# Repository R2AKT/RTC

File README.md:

License addendum - https://github.com/R2AKT/RTC/blob/main/Addendum.txt
# RTC
Real-time clock module (RTC). For connection to the CPU_8080 processor board - https://github.com/R2AKT/CPU_8080.

Based on a real-time clock for RADIO-86RK.

Status: testing and writing the driver.

Модуль часов реального времени (RTC). Для подключения к процессорной плате CPU_8080 - https://github.com/R2AKT/CPU_8080.

На базе часов реального времени для РАДИО-86РК.

Статус: в процессе тестирования и написания драйвера.

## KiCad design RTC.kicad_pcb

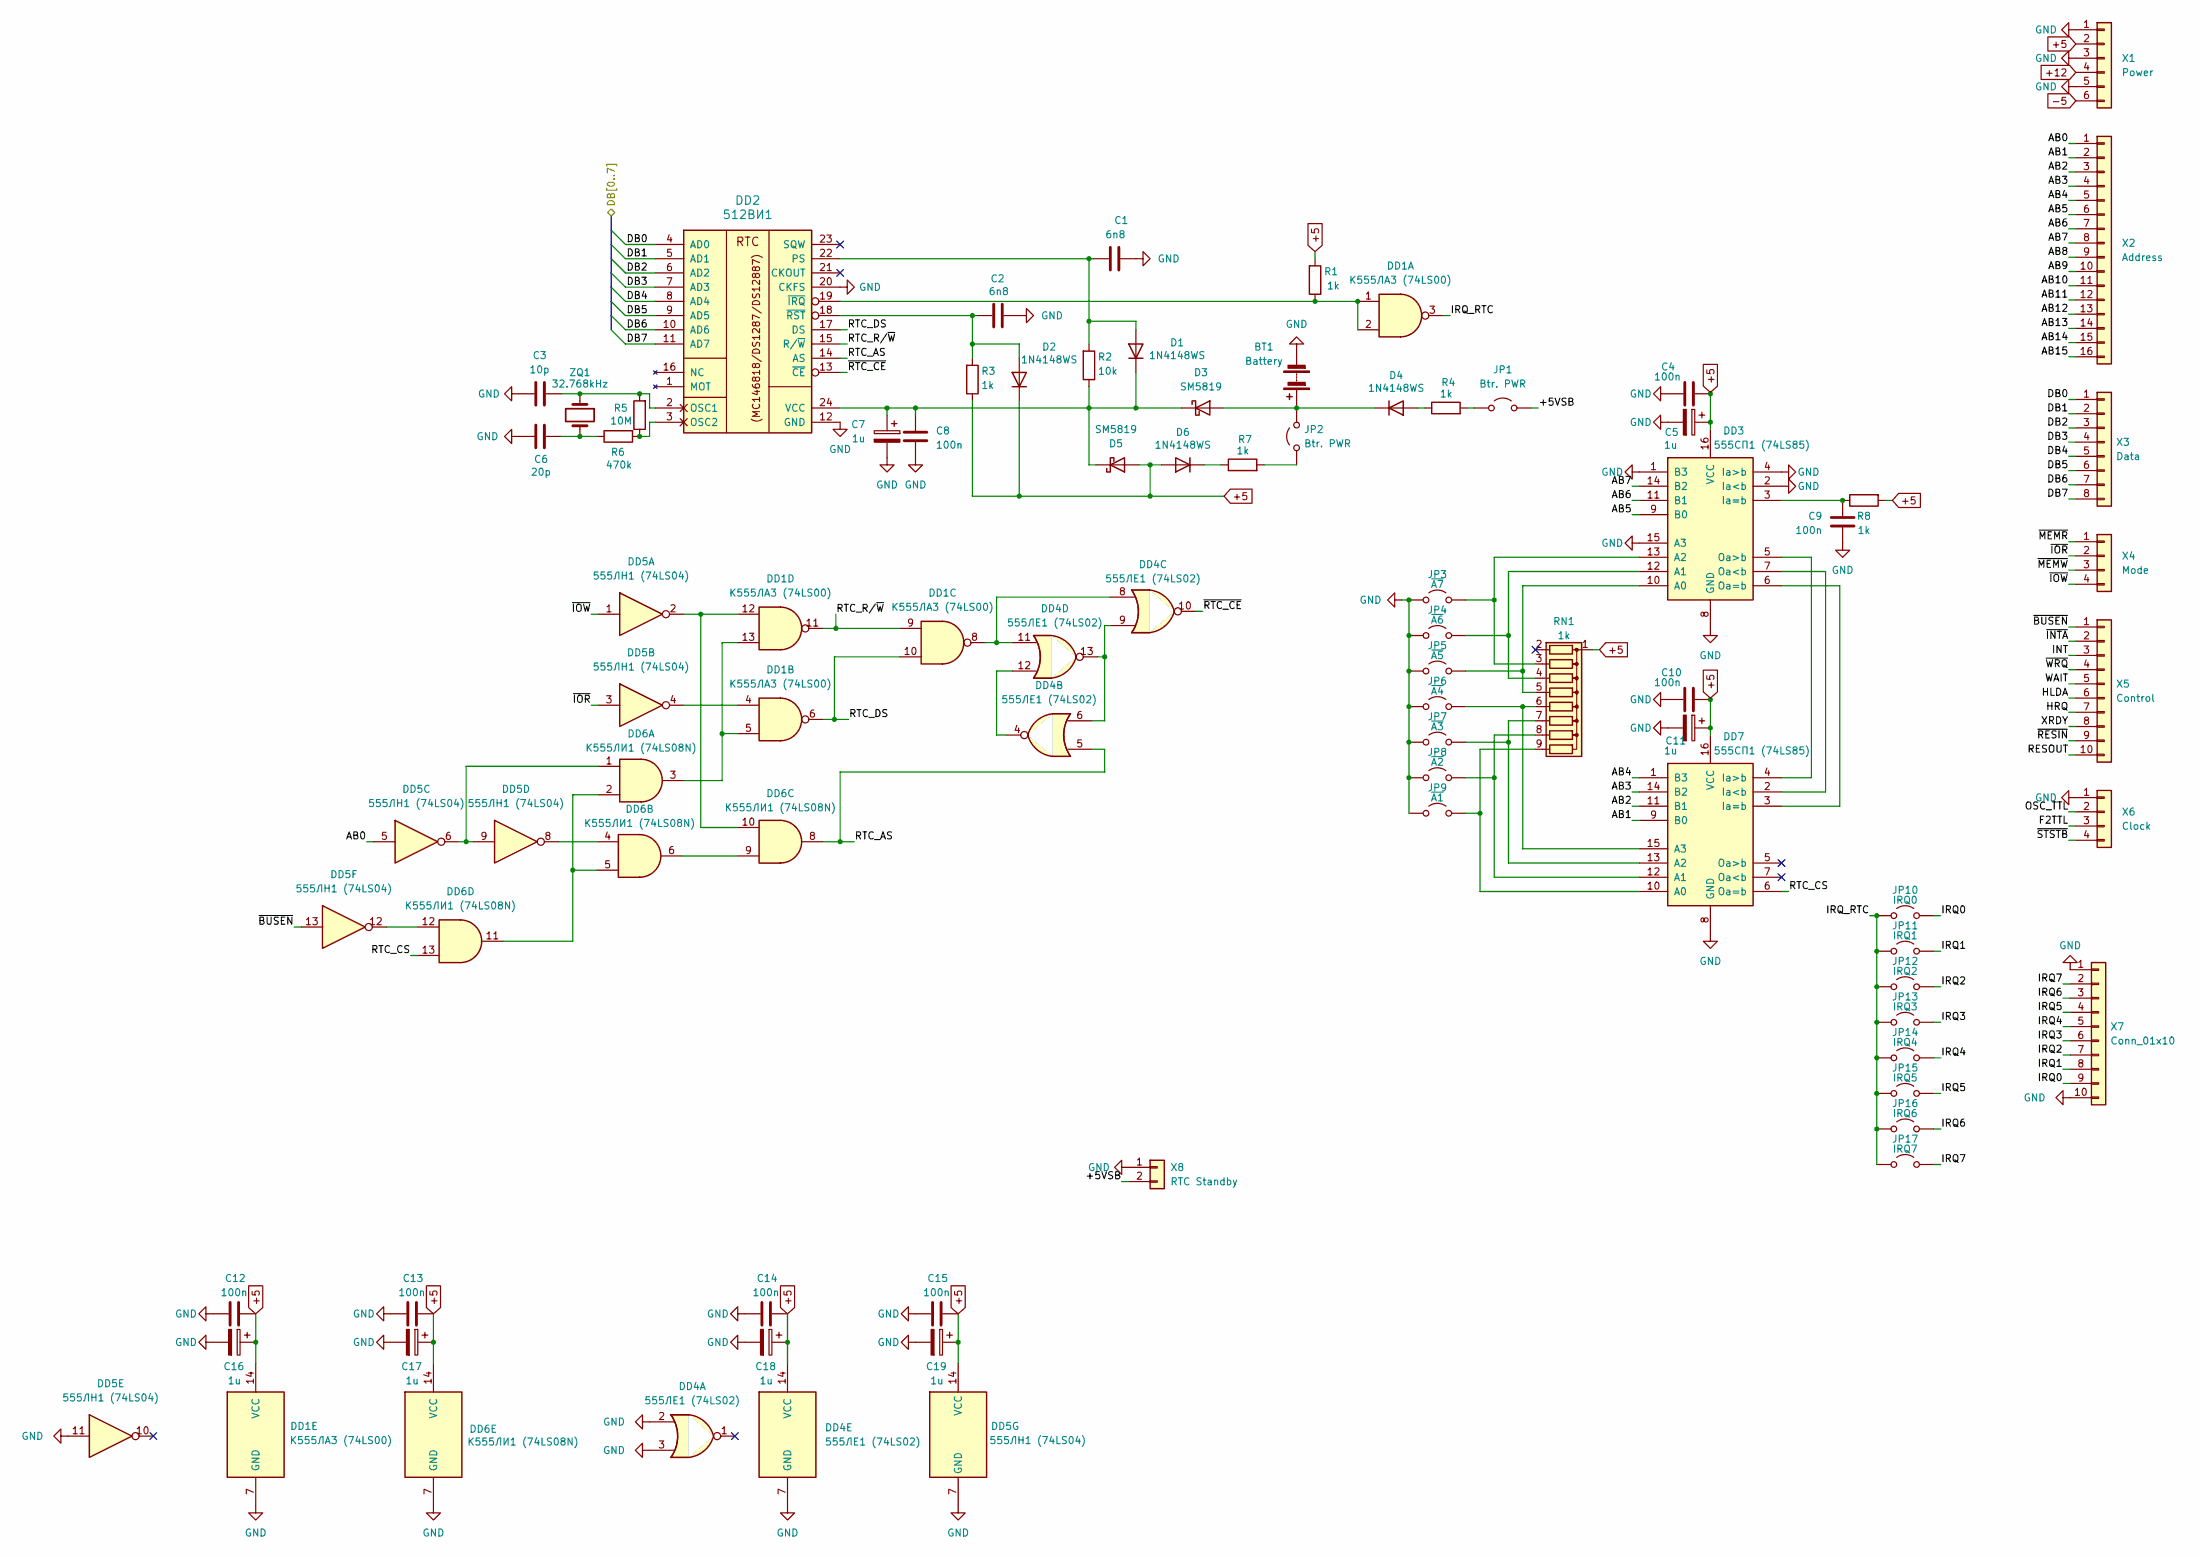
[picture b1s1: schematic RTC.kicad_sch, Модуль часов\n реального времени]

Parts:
BT1: Battery; BatteryHolder_Keystone_500
C1, C2: 6n8; C_0805_2012Metric_Pad1.18x1.45mm_HandSolder
C3: 10p; C_0805_2012Metric_Pad1.18x1.45mm_HandSolder
C4, C8, C9, C10, C12, C13, C14, C15: 100n; C_0805_2012Metric_Pad1.18x1.45mm_HandSolder
C5, C7, C11, C16, C17, C18, C19: 1u; CP_EIA-3216-18_Kemet-A_Pad1.58x1.35mm_HandSolder
C6: 20p; C_0805_2012Metric_Pad1.18x1.45mm_HandSolder
D1, D2, D4, D6: 1N4148WS; D_SOD-323_HandSoldering
D3: SM5819; D_SOD-123F
D5: SM5819; D_SOD-123
DD1: К555ЛА3 (74LS00); DIP-14_W7.62mm_Socket_LongPads
DD2: 512ВИ1; DIP-24_W15.24mm_Socket_LongPads
DD3, DD7: 555СП1 (74LS85); DIP-16_W7.62mm_Socket_LongPads
DD4: 555ЛЕ1 (74LS02); DIP-14_W7.62mm_Socket_LongPads
DD5: 555ЛН1 (74LS04); DIP-14_W7.62mm_Socket_LongPads
DD6: К555ЛИ1 (74LS08N); DIP-14_W7.62mm_Socket_LongPads
JP1, JP2: Btr. PWR; SolderJumper-2_P1.3mm_Open_RoundedPad1.0x1.5mm
JP3: ~{A7}; SolderJumper-2_P1.3mm_Open_RoundedPad1.0x1.5mm
JP4: ~{A6}; SolderJumper-2_P1.3mm_Open_RoundedPad1.0x1.5mm
JP5: ~{A5}; SolderJumper-2_P1.3mm_Open_RoundedPad1.0x1.5mm
JP6: ~{A4}; SolderJumper-2_P1.3mm_Open_RoundedPad1.0x1.5mm
JP7: ~{A3}; SolderJumper-2_P1.3mm_Open_RoundedPad1.0x1.5mm
JP8: ~{A2}; SolderJumper-2_P1.3mm_Open_RoundedPad1.0x1.5mm
JP9: ~{A1}; SolderJumper-2_P1.3mm_Open_RoundedPad1.0x1.5mm
JP10: IRQ0; SolderJumper-2_P1.3mm_Open_RoundedPad1.0x1.5mm
JP11: IRQ1; SolderJumper-2_P1.3mm_Open_RoundedPad1.0x1.5mm
JP12: IRQ2; SolderJumper-2_P1.3mm_Open_RoundedPad1.0x1.5mm
JP13: IRQ3; SolderJumper-2_P1.3mm_Open_RoundedPad1.0x1.5mm
JP14: IRQ4; SolderJumper-2_P1.3mm_Open_RoundedPad1.0x1.5mm
JP15: IRQ5; SolderJumper-2_P1.3mm_Open_RoundedPad1.0x1.5mm
JP16: IRQ6; SolderJumper-2_P1.3mm_Open_RoundedPad1.0x1.5mm
JP17: IRQ7; SolderJumper-2_P1.3mm_Open_RoundedPad1.0x1.5mm
R1, R3, R4, R7, R8: 1k; R_0805_2012Metric_Pad1.20x1.40mm_HandSolder
R2: 10k; R_0805_2012Metric_Pad1.20x1.40mm_HandSolder
R5: 10M; R_0805_2012Metric_Pad1.20x1.40mm_HandSolder
R6: 470k; R_0805_2012Metric_Pad1.20x1.40mm_HandSolder
RN1: 1k; R_Array_SIP9
X1: Power; PinHeader_1x06_P2.54mm_Vertical
X2: Address; PinHeader_1x16_P2.54mm_Vertical
X3: Data; PinHeader_1x08_P2.54mm_Vertical
X4: Mode; PinHeader_1x04_P2.54mm_Vertical
X5: Control; PinHeader_1x10_P2.54mm_Vertical
X6: Clock; PinHeader_1x04_P2.54mm_Vertical
X7: Conn_01x10; PinHeader_1x10_P2.54mm_Vertical
X8: RTC Standby; PinHeader_1x02_P2.54mm_Vertical
ZQ1: 32.768kHz; Crystal_C26-LF_D2.1mm_L6.5mm_Horizontal_1EP_style1

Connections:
+5: C4.1, C5.1, C10.1, C11.1, C12.1, C13.1, C14.1, C15.1, C16.1, C17.1, C18.1, C19.1, D2.1 (K), D5.2 (A), D6.2 (A), DD1.14 (VCC), DD3.16 (VCC), DD4.14 (VCC), DD5.14 (VCC), DD6.14 (VCC), DD7.16 (VCC), R1.2, R3.1, R8.2, RN1.1 (common), X1.2
+12: X1.4
-5: X1.6
/+5VSB: JP1.2 (B), X8.2
/AB0: DD5.5, X2.1
/AB1: DD7.9 (B0), X2.2
/AB2: DD7.11 (B1), X2.3
/AB3: DD7.14 (B2), X2.4
/AB4: DD7.1 (B3), X2.5
/AB5: DD3.9 (B0), X2.6
/AB6: DD3.11 (B1), X2.7
/AB7: DD3.14 (B2), X2.8
/AB8: X2.9
/AB9: X2.10
/AB10: X2.11
/AB11: X2.12
/AB12: X2.13
/AB13: X2.14
/AB14: X2.15
/AB15: X2.16
/DB0: DD2.4 (AD0), X3.1
/DB1: DD2.5 (AD1), X3.2
/DB2: DD2.6 (AD2), X3.3
/DB3: DD2.7 (AD3), X3.4
/DB4: DD2.8 (AD4), X3.5
/DB5: DD2.9 (AD5), X3.6
/DB6: DD2.10 (AD6), X3.7
/DB7: DD2.11 (AD7), X3.8
/F2TTL: X6.3
/HLDA: X5.6
/HRQ: X5.7
/INT: X5.3
/IRQ0: JP10.2 (B), X7.9
/IRQ1: JP11.2 (B), X7.8
/IRQ2: JP12.2 (B), X7.7
/IRQ3: JP13.2 (B), X7.6
/IRQ4: JP14.2 (B), X7.5
/IRQ5: JP15.2 (B), X7.4
/IRQ6: JP16.2 (B), X7.3
/IRQ7: JP17.2 (B), X7.2
/IRQ_RTC: DD1.3, JP10.1 (A), JP11.1 (A), JP12.1 (A), JP13.1 (A), JP14.1 (A), JP15.1 (A), JP16.1 (A), JP17.1 (A)
/OSC_TTL: X6.2
/RESOUT: X5.10
/RTC_AS: DD2.14 (AS), DD4.5, DD6.8
/RTC_CS: DD6.13, DD7.6 (Oa=b)
/RTC_DS: DD1.6, DD1.10, DD2.17 (DS)
/RTC_R/~W: DD1.9, DD1.11, DD2.15 (R/~W)
/WAIT: X5.5
/XRDY: X5.8
/~BUSEN: DD5.13, X5.1
/~INTA: X5.2
/~IOR: DD5.3, X4.2
/~IOW: DD5.1, X4.4
/~MEMR: X4.1
/~MEMW: X4.3
/~RESIN: X5.9
/~RTC_CE: DD2.13 (~CE), DD4.10
/~STSTB: X6.4
/~WRQ: X5.4
GND: BT1.2 (-), C1.2, C2.2, C3.1, C4.2, C5.2, C6.1, C7.2, C8.2, C9.2, C10.2, C11.2, C12.2, C13.2, C14.2, C15.2, C16.2, C17.2, C18.2, C19.2, DD1.7 (GND), DD2.12 (GND), DD2.20 (CKFS), DD3.1 (B3), DD3.2 (Ia<b), DD3.4 (Ia>b), DD3.8 (GND), DD3.15 (A3), DD4.2, DD4.3, DD4.7 (GND), DD5.7 (GND), DD5.11, DD6.7 (GND), DD7.8 (GND), JP3.1 (A), JP4.1 (A), JP5.1 (A), JP6.1 (A), JP7.1 (A), JP8.1 (A), JP9.1 (A), X1.1, X1.3, X1.5, X6.1, X7.1, X7.10, X8.1
unnamed: BT1.1 (+), D3.2 (A), D4.1 (K), JP2.2 (B)
unnamed: C6.2, R6.1, ZQ1.2
unnamed: C1.1, D1.2 (A), DD2.22 (PS), R2.2
unnamed: C7.1, C8.1, D1.1 (K), D3.1 (K), D5.1 (K), DD2.24 (VCC), R2.1
unnamed: C2.1, D2.2 (A), DD2.18 (~RST), R3.2
unnamed: D4.2 (A), R4.1
unnamed: D6.1 (K), R7.1
unnamed: DD1.4, DD5.4
unnamed: DD1.8, DD4.8, DD4.11
unnamed: DD1.12, DD5.2, DD6.10
unnamed: DD1.5, DD1.13, DD6.3
unnamed: C3.2, DD2.2 (OSC1), R5.2, ZQ1.1
unnamed: DD2.3 (OSC2), R5.1, R6.2
unnamed: DD1.1, DD1.2, DD2.19 (~IRQ), R1.1
unnamed: DD3.10 (A0), JP5.2 (B), RN1.5 (R4)
unnamed: DD3.12 (A1), JP4.2 (B), RN1.4 (R3)
unnamed: DD3.13 (A2), JP3.2 (B), RN1.3 (R2)
unnamed: C9.1, DD3.3 (Ia=b), R8.1
unnamed: DD3.7 (Oa<b), DD7.2 (Ia<b)
unnamed: DD3.6 (Oa=b), DD7.3 (Ia=b)
unnamed: DD3.5 (Oa>b), DD7.4 (Ia>b)
unnamed: DD4.4, DD4.12
unnamed: DD4.6, DD4.9, DD4.13
unnamed: DD5.6, DD5.9, DD6.1
unnamed: DD5.8, DD6.4
unnamed: DD5.12, DD6.12
unnamed: DD6.6, DD6.9
unnamed: DD6.2, DD6.5, DD6.11
unnamed: DD7.10 (A0), JP9.2 (B), RN1.9 (R8)
unnamed: DD7.12 (A1), JP8.2 (B), RN1.8 (R7)
unnamed: DD7.13 (A2), JP7.2 (B), RN1.7 (R6)
unnamed: DD7.15 (A3), JP6.2 (B), RN1.6 (R5)
unnamed: JP1.1 (A), R4.2
unnamed: JP2.1 (A), R7.2

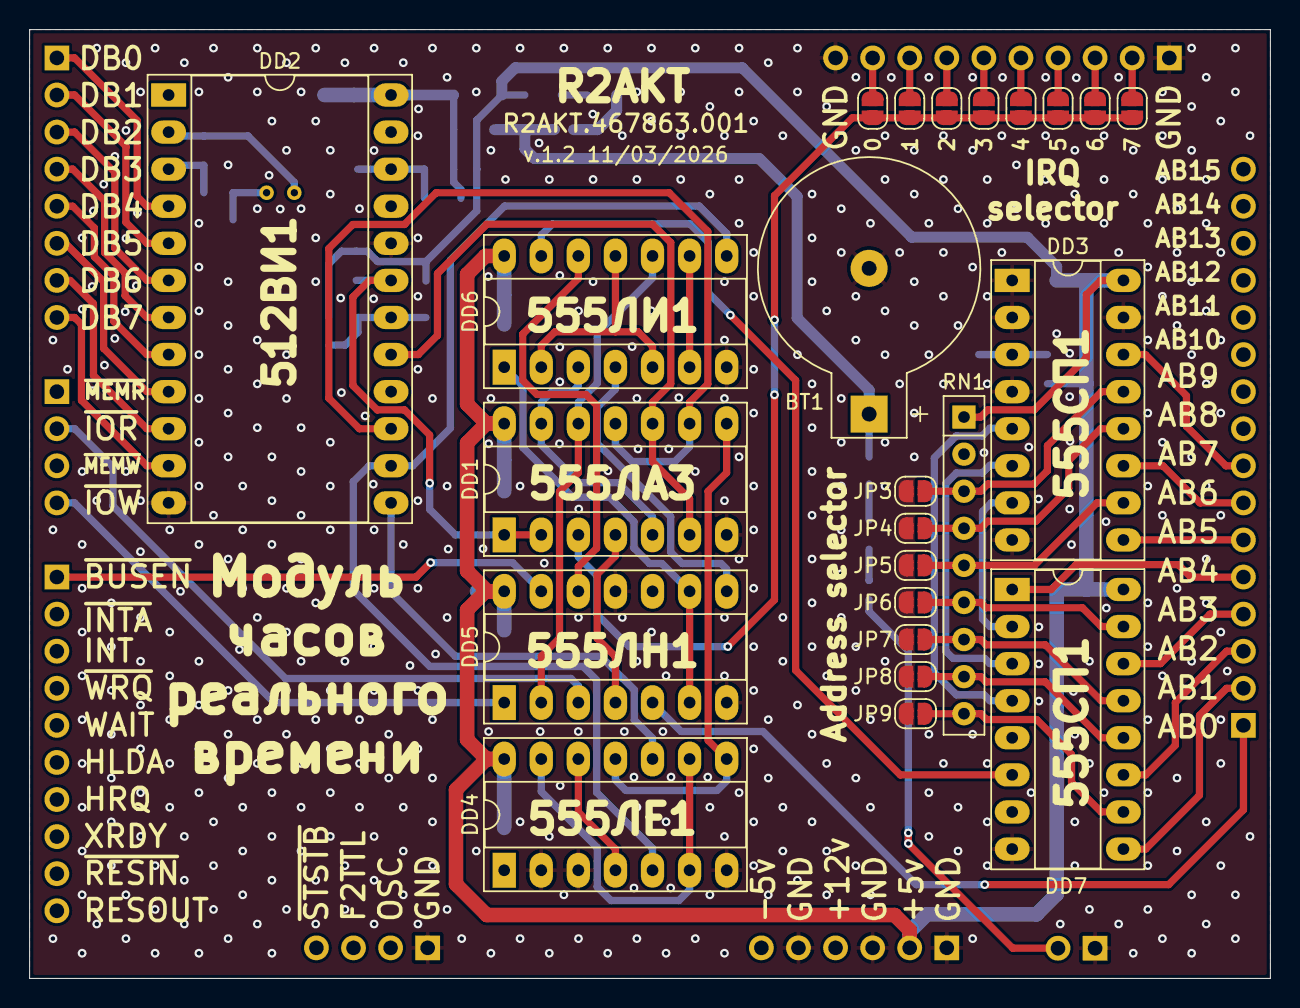
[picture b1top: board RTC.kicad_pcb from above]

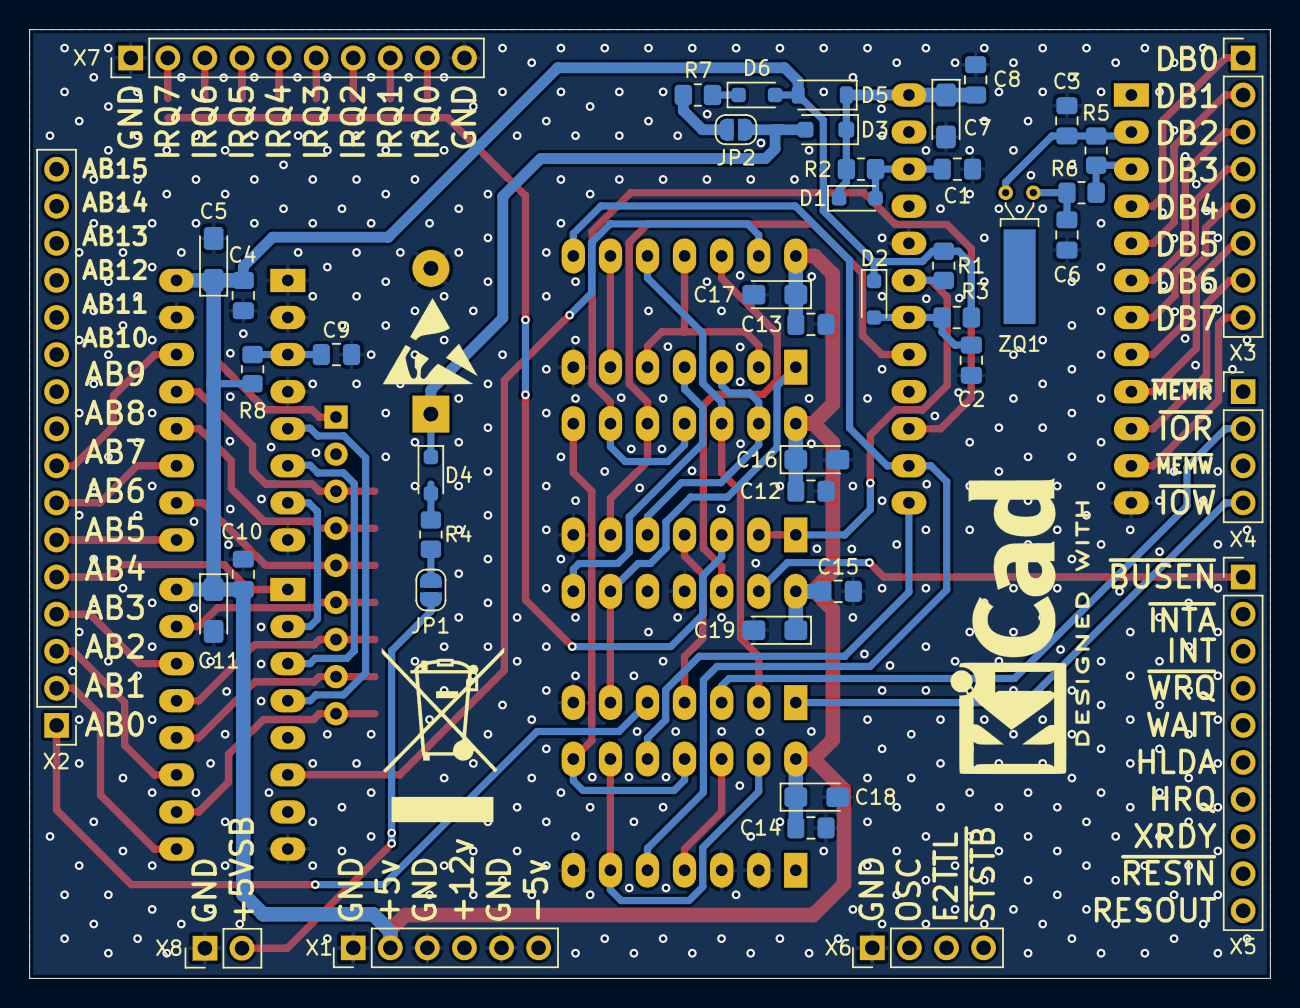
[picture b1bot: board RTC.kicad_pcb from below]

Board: 2 copper layers, 85.0 x 65.0 mm, 68 parts (44 on the bottom side), 70 nets.

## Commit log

2026-02-20 Add files via upload
    Changed chip power-up reset schemtic, added IRQ option, fix silk problem.
    Изменена схема сброса часов при подаче питания, добавлена опция IRQ, исправлены проблемы с шелкографией.
2026-03-11 Add files via upload
    Fix start-up reset issue
    Устранение проблемы начального сброса

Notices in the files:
README.md:
License: MIT
